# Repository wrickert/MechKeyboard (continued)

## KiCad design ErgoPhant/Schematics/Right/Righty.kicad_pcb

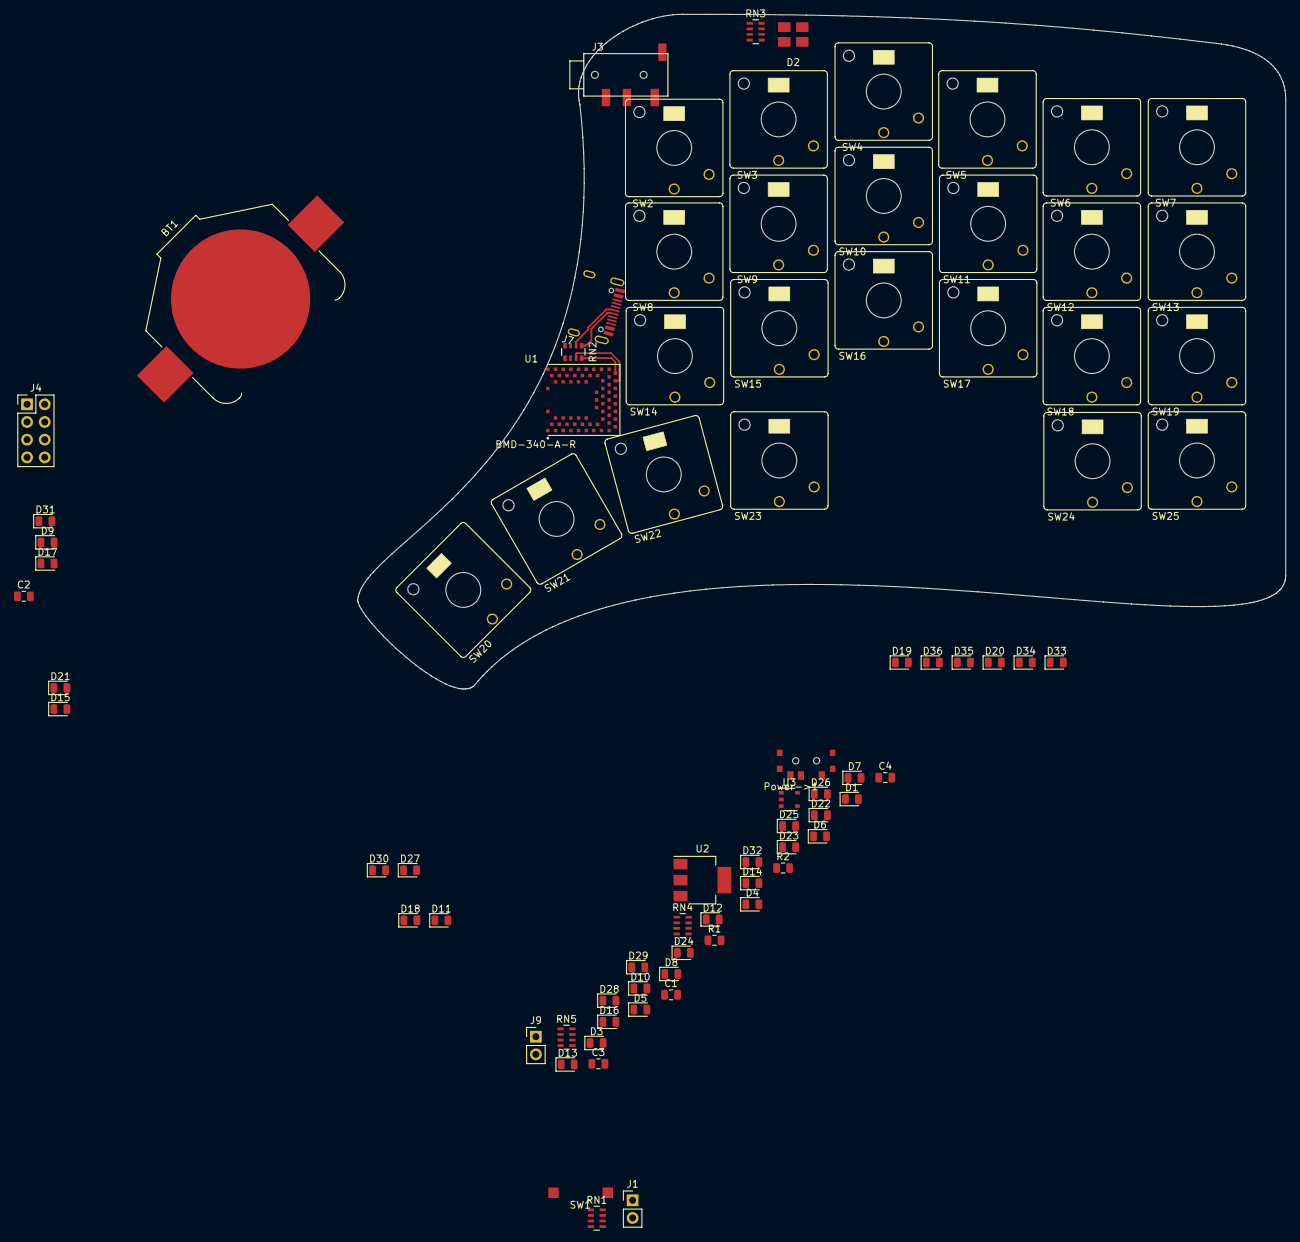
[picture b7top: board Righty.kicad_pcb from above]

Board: 2 copper layers, 133.3 x 96.9 mm, 82 parts (0 on the bottom side), 80 nets.

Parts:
BT1: LIR2450; BatteryHolder_Keystone_3008_1x2450
C1: 4.7uF; C_0805_2012Metric
C2, C3: 1uF; C_0805_2012Metric
C4: 10uF; C_0805_2012Metric
D1, D9, D28, D29, D30, D31, D32, D33, D34, D35, D36: LED_Small; LED_0805_2012Metric
D2: LED_BGRA; EKINGLUX-E6
D3, D4, D5, D6, D7, D8, D10, D11, D12, D13, D14, D15, D16, D17, D18, D19, D20, D21, D22, D23, D24, D25, D26, D27: D; D_0805_2012Metric
J1: PwrRight; PinHeader_1x02_P2.54mm_Vertical
J3: RightConn; PJ-320D-4A_TRRS3.5
J4: Conn_02x04_Odd_Even; PinHeader_2x04_P2.54mm_Vertical
J7: USB_C_Receptacle; USB_C_Receptical-Jing
J9: PwrLeft; PinHeader_1x02_P2.54mm_Vertical
Power->1: SW3; SK-3296S_switch
R1: R_Small; R_0805_2012Metric
R2: 1k; R_0805_2012Metric
RN1: 10k; R_Array_Concave_4x0603
RN2: 27ohm; R_Array_Convex_4x0603
RN3: R_Pack04; R_Array_Concave_4x0603
RN4, RN5: 330; R_Array_Concave_4x0603
SW1: SW_Push; 1TS002E-2500-2500-CT-HYP-Button
SW2, SW3, SW4, SW5, SW6, SW7, SW8, SW9, SW10, SW11, SW12, SW13, SW14, SW15, SW16, SW17, SW18, SW19, SW20, SW21, SW22, SW23, SW24, SW25: Switch; KailhChocolateV2
U1: BMD-340-A-R; RIGADO_BMD-340-A-R
U2: TLV1117-33; SOT-223-3_TabPin2
U3: HX4055M; TSOP-5_1.65x3.05mm_P0.95mm

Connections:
+5V: J7.A4, J7.A9, J7.B4, J7.B9, R2.2, U1.66, U3.4
Blue: RN3.8, U1.56
C7: SW2.2, SW8.2, SW14.2, SW20.2, U1.13
C8: SW3.2, SW9.2, SW15.2, SW21.2, U1.14
C9: SW4.2, SW10.2, SW16.2, SW22.2, U1.19
C10: SW5.2, SW11.2, SW17.2, SW23.2, U1.20
C11: SW6.2, SW12.2, SW18.2, SW24.2, U1.21
C12: SW7.2, SW13.2, SW19.2, SW25.2, U1.22
D+: J7.A6, J7.B6, RN2.2
D-: J7.A7, J7.B7, RN2.1
Green: RN3.7, U1.57
unnamed: C3.2, Power->1.2, U2.2
unnamed: D2.1, RN3.3
unnamed: D2.2, RN3.2
unnamed: D2.3, RN3.1
unnamed: D3.2, SW2.1
unnamed: D4.2, SW3.1
unnamed: D5.2, SW4.1
unnamed: D6.2, SW5.1
unnamed: D7.2, SW6.1
unnamed: D8.2, SW7.1
unnamed: D9.2, RN3.4
unnamed: D10.2, SW8.1
unnamed: D11.2, SW9.1
unnamed: D12.2, SW10.1
unnamed: D13.2, SW11.1
unnamed: D14.2, SW12.1
unnamed: D15.2, SW13.1
unnamed: D16.2, SW14.1
unnamed: D17.2, SW15.1
unnamed: D18.2, SW16.1
unnamed: D19.2, SW17.1
unnamed: D20.2, SW18.1
unnamed: D21.2, SW19.1
unnamed: D22.2, SW20.1
unnamed: D23.2, SW21.1
unnamed: D24.2, SW22.1
unnamed: D25.2, SW23.1
unnamed: D26.2, SW24.1
unnamed: D27.2, SW25.1
unnamed: D28.2, RN4.1
unnamed: D29.2, RN4.2
unnamed: D30.2, RN4.3
unnamed: D31.2, RN4.4
unnamed: D32.2, RN5.1
unnamed: D33.2, RN5.2
unnamed: D34.2, RN5.3
unnamed: D35.2, RN5.4
unnamed: D36.1, U3.1
unnamed: D36.2, R2.1
unnamed: J7.A5, RN1.2
unnamed: J7.B5, RN1.3
unnamed: R1.2, U3.5
unnamed: RN2.7, U1.67
unnamed: RN2.8, U1.68
Other: RN3.5, U1.50
P1.03: J4.8, U1.60
P1.04: J4.6, U1.59
P1.05: J4.7, U1.48
P1.06: J4.5, U1.49
PairButton: SW1.2, U1.51
PairLED: D1.2, U1.52
R1: D3.1, D4.1, D5.1, D6.1, D7.1, D8.1, U1.23
R2: D10.1, D11.1, D12.1, D13.1, D14.1, D15.1, U1.24
R3: D16.1, D17.1, D18.1, D19.1, D20.1, D21.1, U1.27
R4: D22.1, D23.1, D24.1, D25.1, D26.1, D27.1, U1.28
RLed1: RN4.8, U1.31
RLed2: RN4.7, U1.32
RLed3: RN4.6, U1.33
RLed4: RN4.5, U1.34
RLed5: RN5.8, U1.35
RLed6: RN5.7, U1.39
RLed7: RN5.6, U1.37
RLed8: RN5.5, U1.38
Red: RN3.6, U1.58
SWCLK: J4.3, U1.43
SWDIO: J4.1, U1.44
VCC: C1.2, D2.4, J1.1, J3.4, J4.2, J9.1, Power->1.1, U1.17, U1.65
VDDA: BT1.1, C2.2, C4.1, U2.3, U3.3
VSS: BT1.2, C1.1, C2.1, C3.1, C4.2, D1.1, D9.1, D28.1, D29.1, D30.1, D31.1, D32.1, D33.1, D34.1, D35.1, J1.2, J3.1, J4.4, J7.A1, J7.A12, J7.B1, J7.B12, J7.S1, J9.2, R1.1, RN1.6, RN1.7, SW1.1, U1.1, U1.2, U1.3, U1.4, U1.5, U1.16, U1.18, U1.29, U1.30, U1.45, U1.46, U1.47, U1.55, U2.1, U3.2

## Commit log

2021-07-12 Add schematics
2021-08-02 V1 Cafebabe firmware complete
2021-09-20 Start touchstone keyboard
2023-02-07 Updating for hondouras trip
2023-06-15 Added the meetup keyboard
2023-12-12 Try 3 or 4 lol
2023-12-19 added top capture
2023-12-19 Updated for larger static bearing
2024-01-26 Started Keeb
